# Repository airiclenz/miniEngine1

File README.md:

# miniEngine1
An Arduino based single-axis motion-control system for time-lapse photography (the legacy version)

This repository contains all that is needed to build a full miniEngine 1 system. It contains:

	- Software
	- Hardware (PCB CAD files)
	- Documentation
	- Licenses
	
The PCBs and most of the needed parts can be purchased here: http://shop.airiclenz.com  

Notice regarding compilation
----------------------------

The legacy code does not compile with the newest Arduino SDK! Please download the Arduino SDK version 1.0.6 from here: 

http://arduino.cc/en/Main/OldSoftwareReleases

This should compile the code just fine. You will also need to install the RTC library for being able to compile and upload the sketch. Details how to do that can be found in the documentation folder of this repository.

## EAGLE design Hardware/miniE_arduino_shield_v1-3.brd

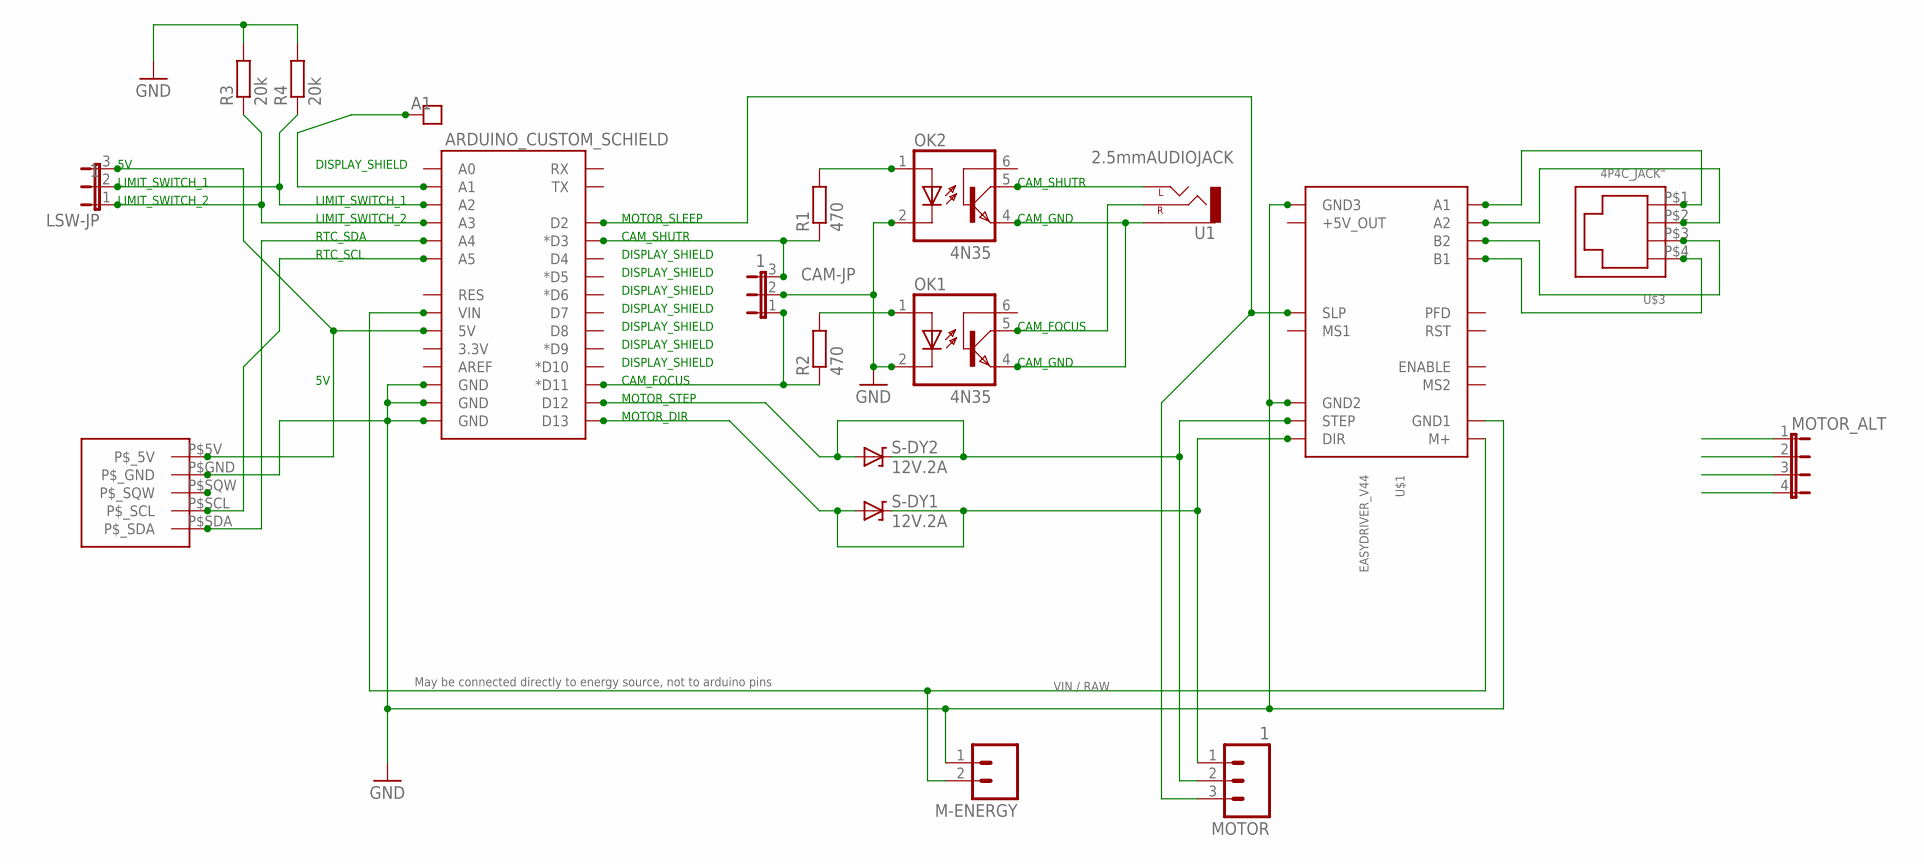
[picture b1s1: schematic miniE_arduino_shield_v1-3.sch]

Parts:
ARDUINO_CUSTOM_SCHIELD: ARDUINO_SHIELDNOLABELS; DUEMILANOVE_SHIELD_NOLABELS
CAM-JP: 1; JP2
LSW-JP: 1; JP2
M-ENERGY: MOLEX_02; 1X02
MOTOR: 1; 1X03
MOTOR_ALT: JP4E; JP4
OK1, OK2: 4N35; DIL06
R1, R2: 470; 0207/10
R3, R4: 20k; 0207/10
S-DY1, S-DY2: 12V.2A; DIODE-ZENER
U1: 2.5mmAUDIOJACK; STEREOJACK2.5MM_STEREOJACK2.5MM
U$1: EASYDRIVER_V44
U$2: SPARKFUN_RTC_MODULE-OPTIONAL; SPARKFUN_RTC_MODULE_OPTIONAL
U$3: 4P4C_JACK"; 4P4C_JACK-ASS-2004-3-4-LP-N-R
U$4: JUMPER_1X1

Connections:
+5V: ARDUINO_CUSTOM_SCHIELD.5V, LSW-JP.3, U$2.P$5V (P$_5V)
A1: MOTOR_ALT.1, U$1.A1, U$3.P$1
A2: MOTOR_ALT.2, U$1.A2, U$3.P$2
B1: MOTOR_ALT.4, U$1.B1, U$3.P$4
B2: MOTOR_ALT.3, U$1.B2, U$3.P$3
CAM_FOCUS: OK1.5 (COL), U1.RING1 (RIGHT), U1.RING2 (RIGHT)
CAM_GND: OK1.4 (EMI), OK2.4 (EMI), U1.SLEEVE
CAM_SHUTTER: OK2.5 (COL), U1.TIP (LEFT)
GND: ARDUINO_CUSTOM_SCHIELD.GND@0 (GND), ARDUINO_CUSTOM_SCHIELD.GND@1 (GND), ARDUINO_CUSTOM_SCHIELD.GND@2 (GND), CAM-JP.2, M-ENERGY.1, OK1.2 (C), OK2.2 (C), R3.2, R4.2, U$1.GND1, U$1.GND2, U$1.GND3, U$2.P$GND (P$_GND)
unnamed: ARDUINO_CUSTOM_SCHIELD.D12, MOTOR.2, S-DY2.P$1 (C), S-DY2.P$2 (A), U$1.STEP
unnamed: ARDUINO_CUSTOM_SCHIELD.D11 (*D11), CAM-JP.1, R2.1
unnamed: ARDUINO_CUSTOM_SCHIELD.D3 (*D3), CAM-JP.3, R1.1
unnamed: ARDUINO_CUSTOM_SCHIELD.D13, MOTOR.1, S-DY1.P$1 (C), S-DY1.P$2 (A), U$1.DIR
unnamed: ARDUINO_CUSTOM_SCHIELD.D2, MOTOR.3, U$1.SLEEP (SLP)
unnamed: OK2.1 (A), R1.2
unnamed: OK1.1 (A), R2.2
unnamed: ARDUINO_CUSTOM_SCHIELD.A2, LSW-JP.2, R4.1
unnamed: ARDUINO_CUSTOM_SCHIELD.A3, LSW-JP.1, R3.1
unnamed: ARDUINO_CUSTOM_SCHIELD.A4, U$2.P$SDA (P$_SDA)
unnamed: ARDUINO_CUSTOM_SCHIELD.A5, U$2.P$SCL (P$_SCL)
unnamed: ARDUINO_CUSTOM_SCHIELD.A1, U$4.P$1
VIN: ARDUINO_CUSTOM_SCHIELD.VIN, M-ENERGY.2, U$1.M+

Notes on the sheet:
CAM_FOCUS
CAM_GND
CAM_SHUTR
DISPLAY_SHIELD
MOTOR_SLEEP
MOTOR_STEP
MOTOR_DIR
LIMIT_SWITCH_1
LIMIT_SWITCH_2
RTC_SDA
RTC_SCL
VIN / RAW
May be connected directly to energy source, not to arduino pins

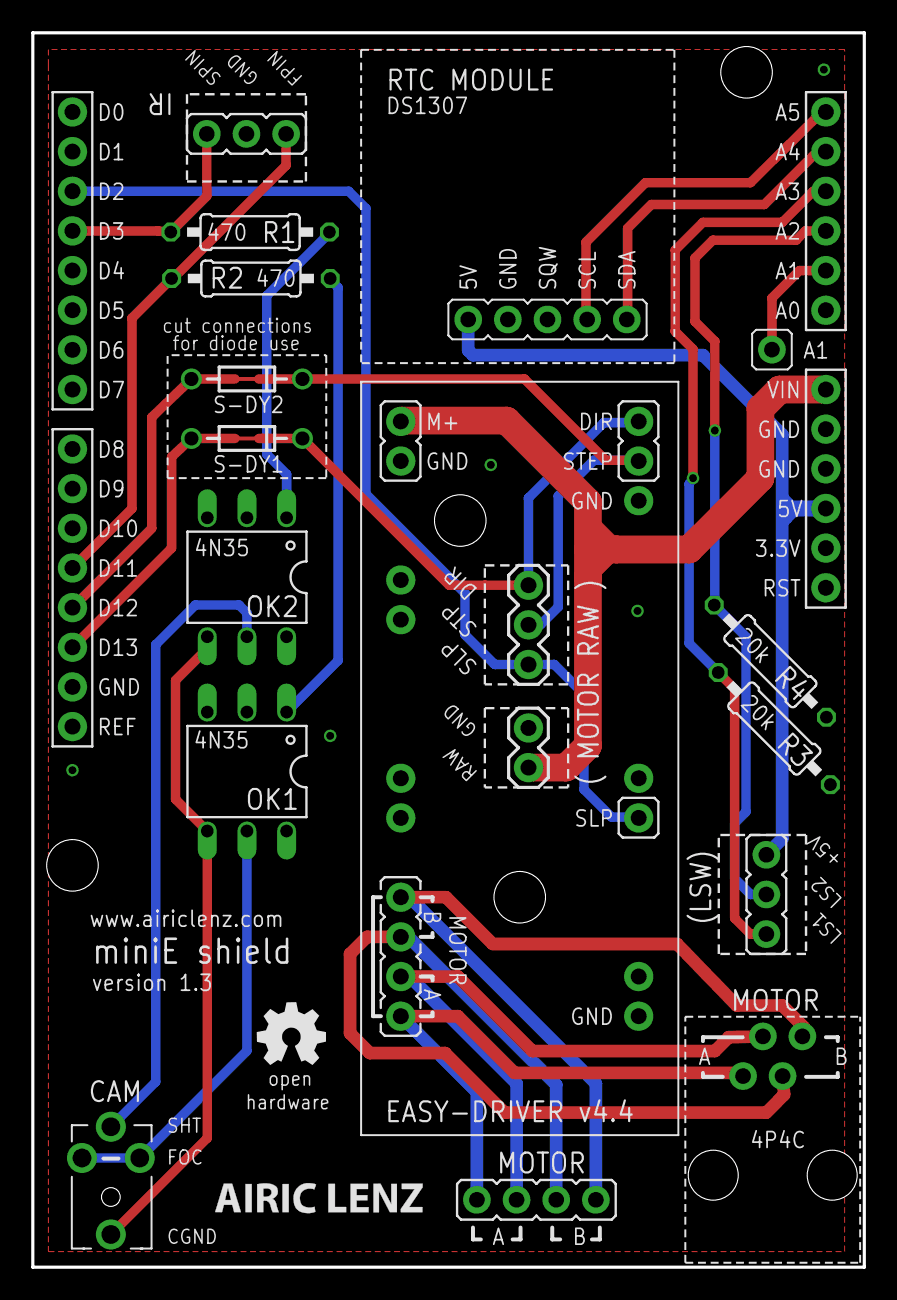
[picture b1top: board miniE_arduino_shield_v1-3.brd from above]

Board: 4 copper layers, 53.3 x 79.1 mm, 19 parts (0 on the bottom side), 22 nets.

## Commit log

2015-02-23 initial commit to GitHub
2015-02-23 Changelog Update
2015-02-23 corrected version and release year
2015-03-02 updated documentation
2015-03-10 added documentation for acrylic enclosure
2016-05-19 Removed some illegal characters
2019-05-07 Adaption to the latest Arduinio SDK version
